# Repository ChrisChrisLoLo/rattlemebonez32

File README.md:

# rattlemebonez32

### A 32 key monoblock with minimal choc spacing and vibes

This pocket board is the bigger cousin to the [idawgz32](https://github.com/ChrisChrisLoLo/idawgz32). Same minimalist key layout, more egonomic form factor. Uses a CH552 as its MCU, and runs FAK firmware.

# Status
PCBs include a choc variant and a ks33 variant. Both work, though I highly recommend the choc variant as it's much easier to
assmble (ks33 switches do not snap into the board, making soldering difficult but possible).

The keys on this board are minimally spaced (15mm x 15mm), and as such will need special keycaps. 

This repo has a minimally spaced choc keycap based on the Philidelphia minimalist. You will likely need a 3D printer such as a Bambu Lab A1/A1 mini/P1P/P1S and set the slicing layer resolution to 0.08mm for best results. Printers like the Prusa i3/mini may also work, but have not been tested.

# Case
The case files can be found in the `case` directory.

The case comes in two parts, the top section and the bottom section.

## PCB
You can find the PCB source files in the `pcb` folder. The BOM files can be found in this folder.

## Directory Structure
- `case`
    You can find the files you need in this folder to print out a case and choc switches for the keyboard
- `drafts`
    Stores any ergogen or intermediate information used in making the case
- `pcb`
    Kicad project relating to the project. Contains the BOM, placement files, and gerbers
   
## BOM
- 1 PCBA
  - The PCB will include all electrical parts required, including switches.
- 1 Aluminum CNC upper case or 3DP upper case (technically optional, but strongly recommended)
- 1 Alumminum CNC lower case or CNC lower case
- 12 3mm M1.6 screws (go for flathead for a more flush fit, though other head types should also work)
- 8 1-2mm bumpons (something like Sj5302 is a good place to start)

## Assembly
Flash the pcb with my FAK branch (see below section). Bootmagic is enabled, so using the top left key to flash from here on out is doable.

Pop the 3D printed buttons/keycaps into the case. and screw the bottom case to the PCBA. Then place on the top and screw the top case to the PCBA.

Finally, place on the rubber bumpons

## Firmware
Branch and fork of FAK Firmware can be found here:
https://github.com/ChrisChrisLoLo/fak/tree/rattlemebonez32

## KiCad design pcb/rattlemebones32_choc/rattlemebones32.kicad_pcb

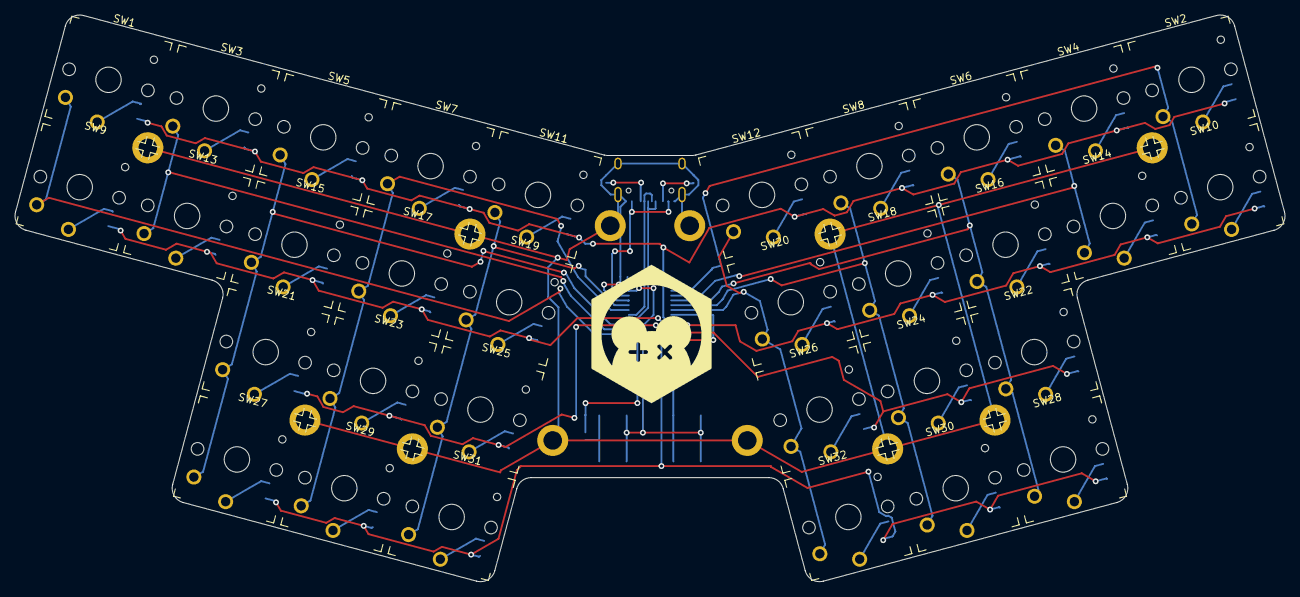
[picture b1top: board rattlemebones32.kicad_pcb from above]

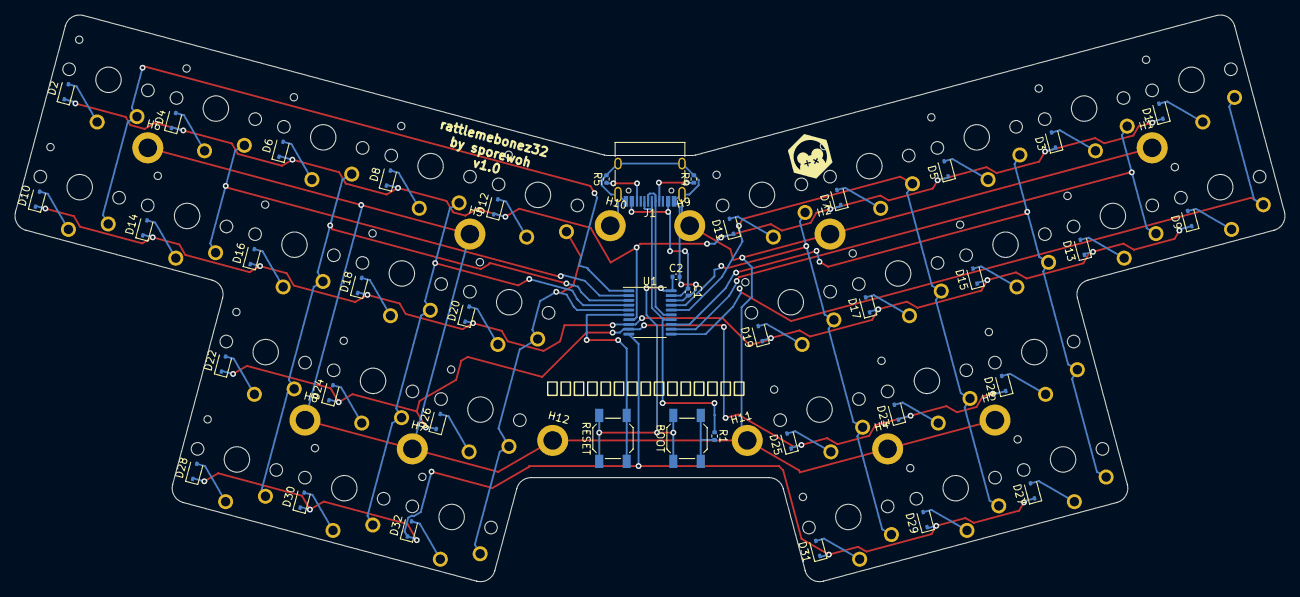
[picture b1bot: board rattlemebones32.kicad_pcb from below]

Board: 2 copper layers, 171.3 x 76.4 mm, 85 parts (53 on the bottom side), 55 nets.

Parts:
C1, C2: 100nF; C_0402_1005Metric
D1, D2, D3, D4, D5, D6, D7, D8, D9, D10, D11, D12, D13, D14, D15, D16, D17, D18, D19, D20, D21, D22, D23, D24, D25, D26, D27, D28, D29, D30, D31, D32: D_Small; D_SOD-323
H1, H2, H3, H4, H5, H6, H7, H8, H9, H10, H11, H12: MountingHole_Pad; SMTSO-M1.6
J1: USB_C_Receptacle_USB2.0; USB_C_Receptacle_HRO_TYPE-C-31-M-12
R1: 10k; R_0402_1005Metric
R4, R5: 5.1k; R_0402_1005Metric
SW1, SW2, SW3, SW4, SW5, SW6, SW7, SW8, SW9, SW10, SW11, SW12, SW13, SW14, SW15, SW16, SW17, SW18, SW19, SW20, SW21, SW22, SW23, SW24, SW25, SW26, SW27, SW28, SW29, SW30, SW31, SW32: SW_Push; SW_PG1350
SW33: BOOT; SW_SPST_SKQG_WithStem
SW34: RESET; SW_SPST_SKQG_WithStem
U1: CH552T; TSSOP-20_4.4x6.5mm_P0.65mm

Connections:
+3.3V: C2.1, SW33.2, SW34.2, U1.20 (V33)
BOOT: R1.2, SW33.1
CC1: J1.A5 (CC1), R4.1
CC2: J1.B5 (CC2), R5.1
GND: C1.2, C2.2, H1.1, H2.1, H3.1, H4.1, H5.1, H6.1, H7.1, H8.1, H9.1, H10.1, H11.1, H12.1, J1.A1 (GND), J1.A12 (GND), J1.B1 (GND), J1.B12 (GND), J1.S1 (SHIELD), R4.2, R5.2, U1.18 (GND/VSS)
unnamed: D1.2 (A), SW1.1
unnamed: D2.2 (A), SW2.1
unnamed: D3.2 (A), SW3.1
unnamed: D4.2 (A), SW4.1
unnamed: D5.2 (A), SW5.1
unnamed: D6.2 (A), SW6.1
unnamed: D7.2 (A), SW7.1
unnamed: D8.2 (A), SW8.1
unnamed: D9.2 (A), SW9.1
unnamed: D10.2 (A), SW10.1
unnamed: D11.2 (A), SW11.1
unnamed: D12.2 (A), SW12.1
unnamed: D13.2 (A), SW13.1
unnamed: D14.2 (A), SW14.1
unnamed: D15.2 (A), SW15.1
unnamed: D16.2 (A), SW16.1
unnamed: D17.2 (A), SW17.1
unnamed: D18.2 (A), SW18.1
unnamed: D19.2 (A), SW19.1
unnamed: D20.2 (A), SW20.1
unnamed: D21.2 (A), SW21.1
unnamed: D22.2 (A), SW22.1
unnamed: D23.2 (A), SW23.1
unnamed: D24.2 (A), SW24.1
unnamed: D25.2 (A), SW25.1
unnamed: D26.2 (A), SW26.1
unnamed: D27.2 (A), SW27.1
unnamed: D28.2 (A), SW28.1
unnamed: D29.2 (A), SW29.1
unnamed: D30.2 (A), SW30.1
unnamed: D31.2 (A), SW31.1
unnamed: D32.2 (A), SW32.1
RST: SW34.1, U1.6 (RST/T2EX_/CAP2_)
UDM: J1.A7 (D-), J1.B7 (D-), U1.15 (P3.7/UDM)
UDP: J1.A6 (D+), J1.B6 (D+), R1.1, U1.14 (P3.6/UDP)
VBUS: C1.1, J1.A4 (VBUS), J1.A9 (VBUS), J1.B4 (VBUS), J1.B9 (VBUS), U1.19 (VCC/VDD)
col1: SW2.2, SW10.2, U1.1 (P3.2/TXD1_/INT0/VBUS1/AIN3)
col2: SW4.2, SW14.2, U1.2 (P1.4/T2_/CAP1_/SCS/TIN2/UCC1/AIN1)
col3: SW6.2, SW16.2, SW22.2, SW28.2, U1.3 (P1.5/MOSI/PWM1/TIN3/UCC2/AIN2)
col4: SW8.2, SW18.2, SW24.2, SW30.2, U1.4 (P1.6/MISO/RXD1/TIN4)
col5: SW12.2, SW20.2, SW26.2, SW32.2, U1.5 (P1.7/SCK/TXD1/TIN5)
col6: SW11.2, SW19.2, SW25.2, SW31.2, U1.17 (P1.2/XI/RXD_)
col7: SW7.2, SW17.2, SW23.2, SW29.2, U1.16 (P1.3/XO/TXD_)
col8: SW5.2, SW15.2, SW21.2, SW27.2, U1.13 (P3.5/T1)
col9: SW3.2, SW13.2, U1.12 (P3.4/PWM2/RXD1_/T0)
col10: SW1.2, SW9.2, U1.11 (P3.3/INT1)
row1: D1.1 (K), D2.1 (K), D3.1 (K), D4.1 (K), D5.1 (K), D6.1 (K), D7.1 (K), D8.1 (K), D11.1 (K), D12.1 (K), U1.7 (P1.0/T2/CAP1/TIN0)
row2: D9.1 (K), D10.1 (K), D13.1 (K), D14.1 (K), D15.1 (K), D16.1 (K), D17.1 (K), D18.1 (K), D19.1 (K), D20.1 (K), U1.8 (P1.1/T2EX/CAP2/TIN1/VBUS2/AIN0)
row3: D21.1 (K), D22.1 (K), D23.1 (K), D24.1 (K), D25.1 (K), D26.1 (K), U1.9 (P3.1/PWM2_/TXD)
row4: D27.1 (K), D28.1 (K), D29.1 (K), D30.1 (K), D31.1 (K), D32.1 (K), U1.10 (P3.0/PWM1_/RXD)

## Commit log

2024-02-20 pcb init
2024-02-20 ergogen init
2024-04-08 exports and case init
2024-04-08 init keycaps
2024-04-08 add images
2024-04-08 rename ks33 variant folder
2024-04-08 init README
